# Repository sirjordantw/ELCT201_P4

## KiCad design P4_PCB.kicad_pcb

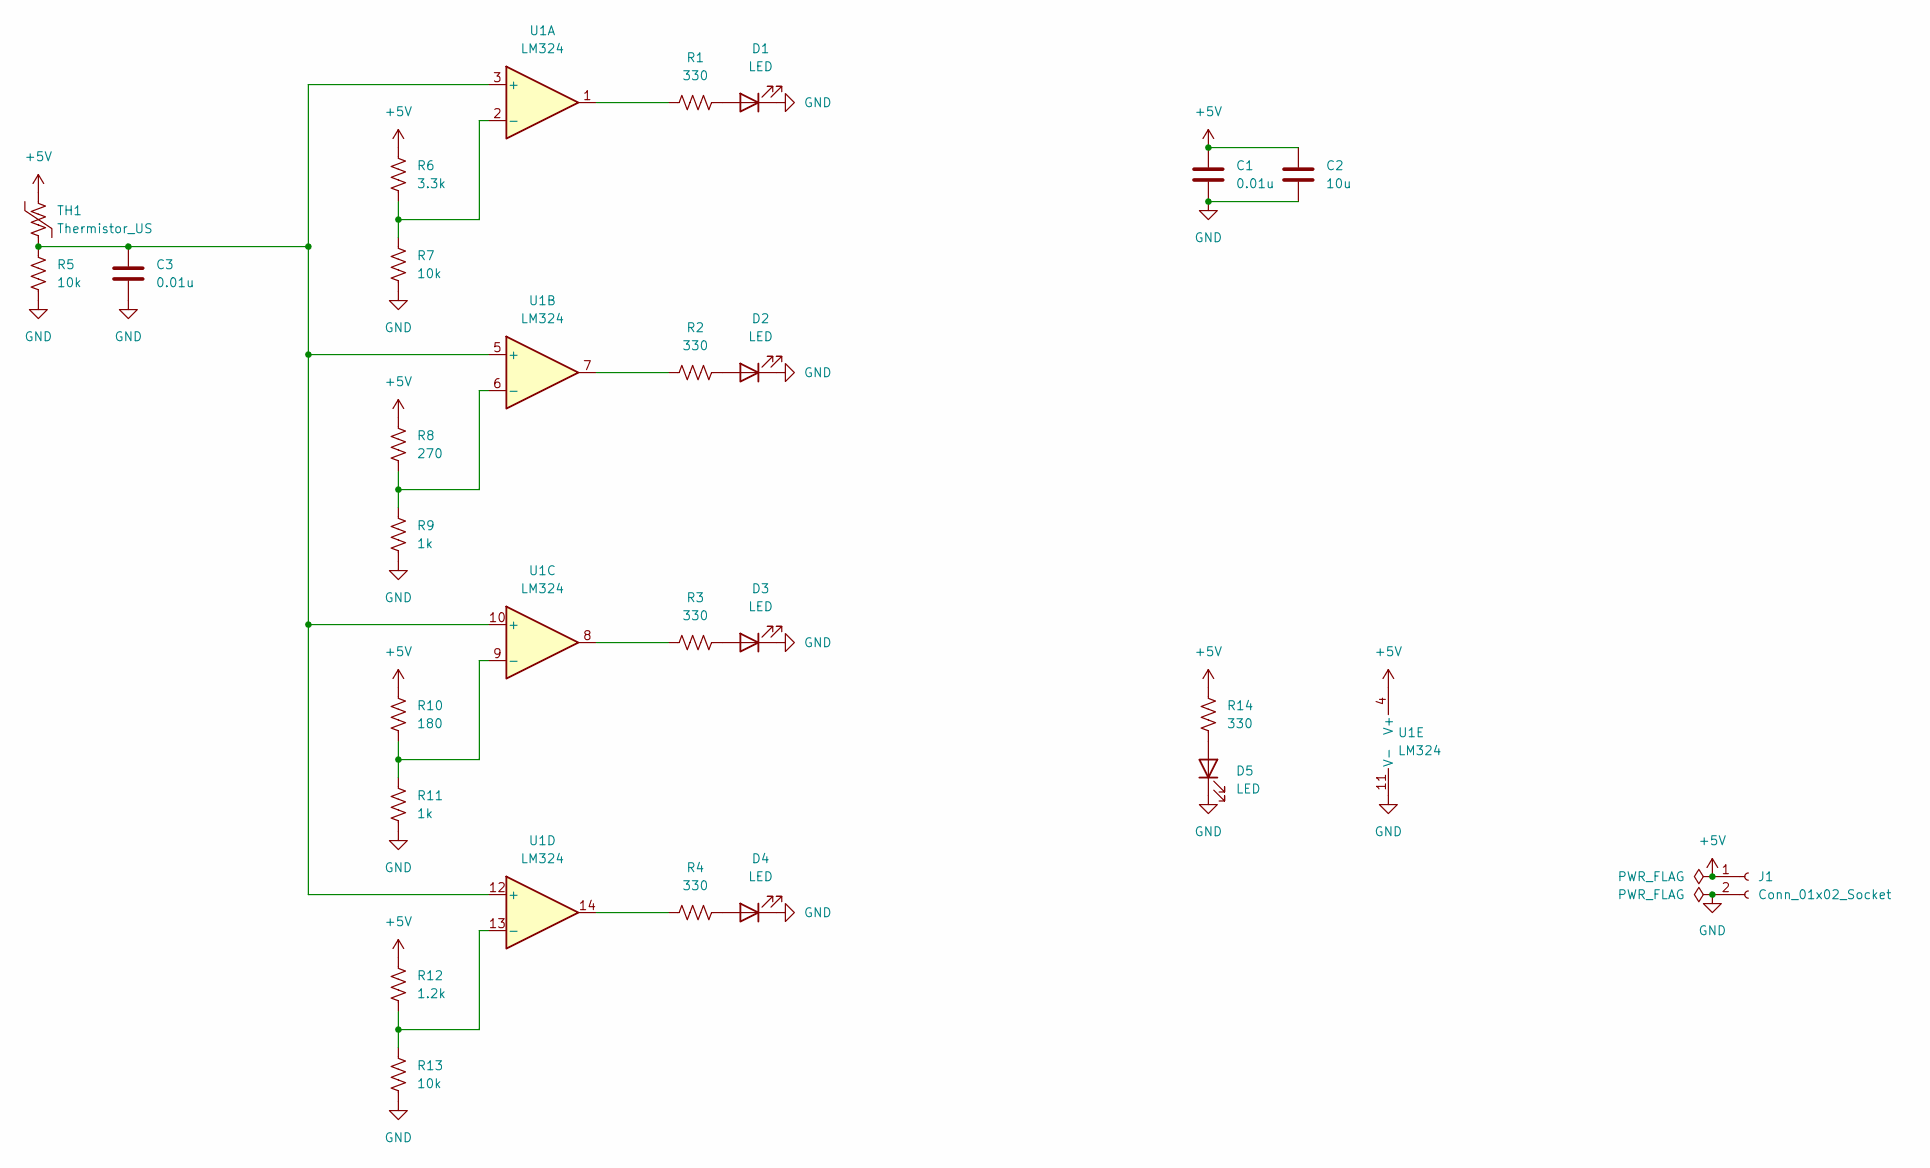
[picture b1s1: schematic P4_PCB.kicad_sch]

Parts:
C1, C3: 0.01u; C_Disc_D6.0mm_W2.5mm_P5.00mm
C2: 10u; CP_Radial_D5.0mm_P2.50mm
D1, D2, D3, D4, D5: LED; LED_D5.0mm
J1: Conn_01x02_Socket; PinHeader_1x02_P2.54mm_Vertical
R1, R2, R3, R4, R14: 330; R_Axial_DIN0614_L14.3mm_D5.7mm_P15.24mm_Horizontal
R5, R7, R13: 10k; R_Axial_DIN0614_L14.3mm_D5.7mm_P15.24mm_Horizontal
R6: 3.3k; R_Axial_DIN0614_L14.3mm_D5.7mm_P15.24mm_Horizontal
R8: 270; R_Axial_DIN0614_L14.3mm_D5.7mm_P15.24mm_Horizontal
R9, R11: 1k; R_Axial_DIN0614_L14.3mm_D5.7mm_P15.24mm_Horizontal
R10: 180; R_Axial_DIN0614_L14.3mm_D5.7mm_P15.24mm_Horizontal
R12: 1.2k; R_Axial_DIN0614_L14.3mm_D5.7mm_P15.24mm_Horizontal
TH1: Thermistor_US; R_Axial_DIN0204_L3.6mm_D1.6mm_P2.54mm_Vertical
U1: LM324; DIP-14_W7.62mm_Socket_LongPads

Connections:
+5V: C1.1, C2.1, J1.1, R6.1, R8.1, R10.1, R12.1, R14.1, TH1.1, U1.4 (V+)
GND: C1.2, C2.2, C3.2, D1.1 (K), D2.1 (K), D3.1 (K), D4.1 (K), D5.1 (K), J1.2, R5.2, R7.2, R9.2, R11.2, R13.2, U1.11 (V-)
unnamed: D1.2 (A), R1.2
unnamed: D2.2 (A), R2.2
unnamed: D3.2 (A), R3.2
unnamed: D4.2 (A), R4.2
unnamed: D5.2 (A), R14.2
unnamed: R1.1, U1.1
unnamed: R2.1, U1.7
unnamed: R3.1, U1.8
unnamed: R4.1, U1.14
unnamed: C3.1, R5.1, TH1.2, U1.3 (+), U1.5 (+), U1.10 (+), U1.12 (+)
unnamed: R6.2, R7.1, U1.2 (-)
unnamed: R8.2, R9.1, U1.6 (-)
unnamed: R10.2, R11.1, U1.9 (-)
unnamed: R12.2, R13.1, U1.13 (-)

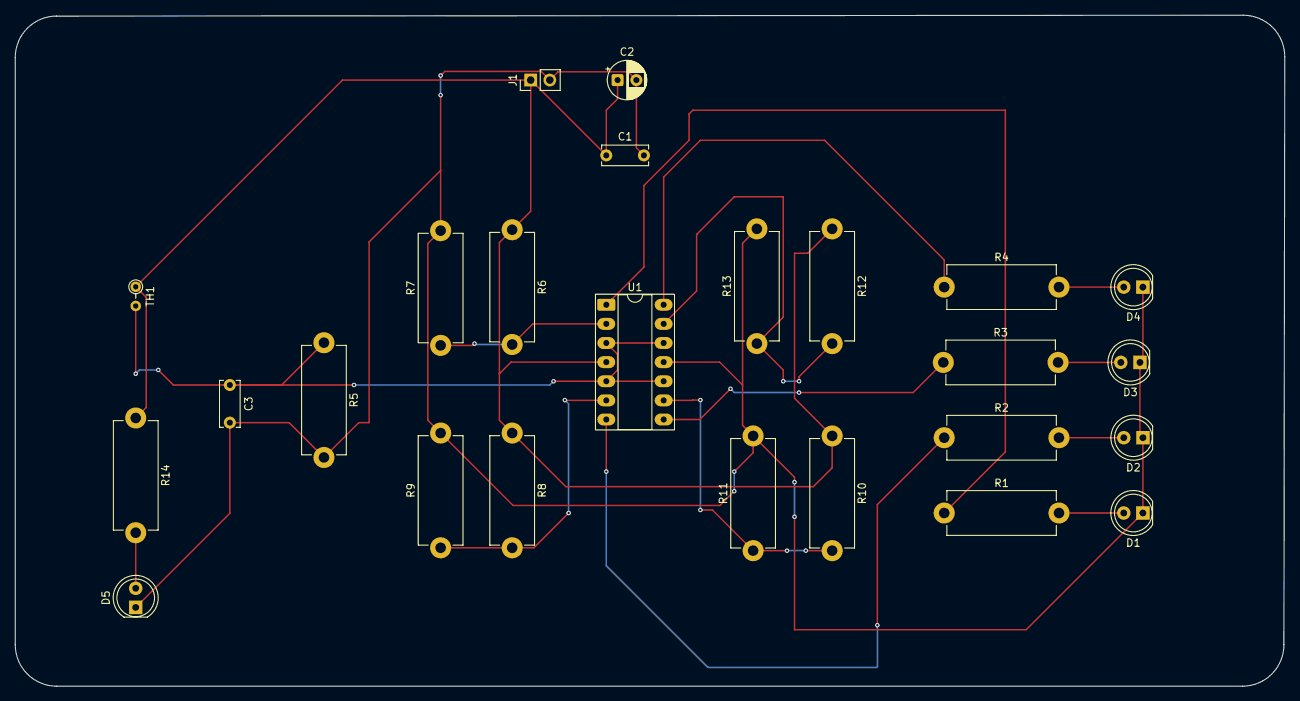
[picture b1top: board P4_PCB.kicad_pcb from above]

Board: 2 copper layers, 168.6 x 89.1 mm, 25 parts (0 on the bottom side), 16 nets.
